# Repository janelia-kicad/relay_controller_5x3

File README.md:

# relay_controller_5x3

Authors:

    Peter Polidoro <polidorop@janelia.hhmi.org>

License:

    BSD

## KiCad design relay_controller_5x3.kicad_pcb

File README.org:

#+TITLE: relay_controller_5x3
#+AUTHOR: Peter Polidoro
#+EMAIL: peter@polidoro.io

* Repository Information
  - Author :: Peter Polidoro
  - License :: Open-Source Hardware

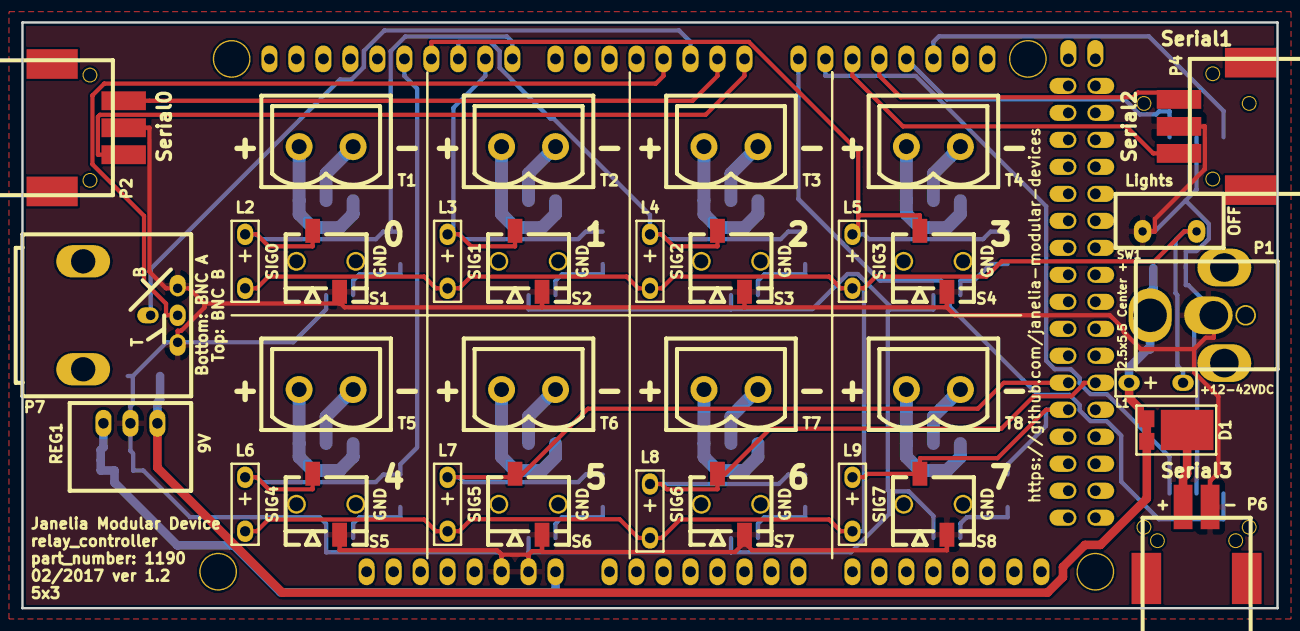
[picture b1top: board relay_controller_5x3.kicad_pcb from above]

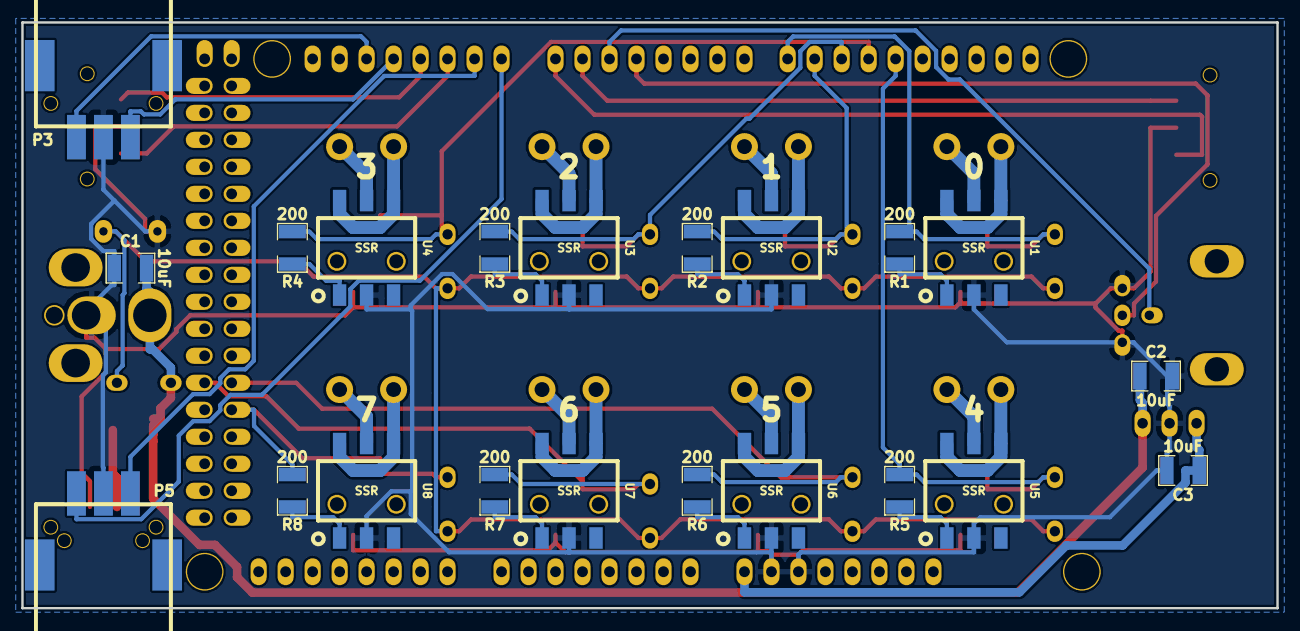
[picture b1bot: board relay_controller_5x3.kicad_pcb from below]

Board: 2 copper layers, 118.1 x 55.1 mm, 55 parts (21 on the bottom side), 47 nets.

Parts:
ARDUINO1: ARDUINO_MEGA; ARDUINO_MEGA_SHIELD
C1, C2, C3: 10uF; SM1210
D1: diode_schottky_45V_10A; CFP15
L1: LED_24V; LED_555-3XXX
L2, L3, L4, L5, L6, L7, L8, L9: LED_5V_GRN; LED_555-3XXX
P1: PWR_JACK_2.5x5.5; DCJACK_2PIN_HIGHCURRENT
P2, P3, P4, P5: HEADER_01X03_SMD_RA; Header_3_Pin_SMD_RA
P6: HEADER_01X02_SMD_RA; Header_2_Pin_SMD_RA
P7: BNC_DOUBLE_RA; BNC_DOUBLE
R1, R2, R3, R4, R5, R6, R7, R8: 200; SM1210
REG1: CONV_DC_DC_9V_1A; DC_DC_CONV_R78C
S1, S2, S3, S4, S5, S6, S7, S8: HEADER_01X02_SMD_SHR; Header_2_Pin_SMD_SHR
SW1: SPST_SLIDE_AS
T1, T2, T3, T4, T5, T6, T7, T8: TERM_BLK_HDR_2POS_VERT_0.2IN
U1, U2, U3, U4, U5, U6, U7, U8: SSR; 6-SMD-GW-0.3IN

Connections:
/BNC_A: ARDUINO1.2, P7.1
/BNC_B: ARDUINO1.3, P7.3
/LED_GND: L1.2, L2.2, L3.2, L4.2, L5.2, L6.2, L7.2, L8.2, L9.2, SW1.3
/OUT_0+: T1.1, U1.4, U1.6
/OUT_0-: T1.2, U1.5
/OUT_1+: T2.1, U2.4, U2.6
/OUT_1-: T2.2, U2.5
/OUT_2+: T3.1, U3.4, U3.6
/OUT_2-: T3.2, U3.5
/OUT_3+: T4.1, U4.4, U4.6
/OUT_3-: T4.2, U4.5
/OUT_4+: T5.1, U5.4, U5.6
/OUT_4-: T5.2, U5.5
/OUT_5+: T6.1, U6.4, U6.6
/OUT_5-: T6.2, U6.5
/OUT_6+: T7.1, U7.4, U7.6
/OUT_6-: T7.2, U7.5
/OUT_7+: T8.1, U8.4, U8.6
/OUT_7-: T8.2, U8.5
/RX0: ARDUINO1.0, P2.1
/RX1: ARDUINO1.19, P3.1
/RX2: ARDUINO1.17, P4.1
/RX3: ARDUINO1.15, P5.1
/SIGNAL_0: ARDUINO1.8, L2.1, R1.2, S1.1
/SIGNAL_1: ARDUINO1.9, L3.1, R2.2, S2.1
/SIGNAL_2: ARDUINO1.10, L4.1, R3.2, S3.1
/SIGNAL_3: ARDUINO1.11, L5.1, R4.2, S4.1
/SIGNAL_4: ARDUINO1.12, L6.1, R5.2, S5.1
/SIGNAL_5: ARDUINO1.44, L7.1, R6.2, S6.1
/SIGNAL_6: ARDUINO1.45, L8.1, R7.2, S7.1
/SIGNAL_7: ARDUINO1.46, L9.1, R8.2, S8.1
/TX0: ARDUINO1.1, P2.3
/TX1: ARDUINO1.18, P3.3
/TX2: ARDUINO1.16, P4.3
/TX3: ARDUINO1.14, P5.3
/V_IN: ARDUINO1.V_IN, C3.1, REG1.3
GND: ARDUINO1.GND1, ARDUINO1.GND2, C1.2, C2.2, C3.2, P1.2, P2.2, P3.2, P4.2, P5.2, P6.1, P7.2, P7.4, REG1.2, S1.2, S2.2, S3.2, S4.2, S5.2, S6.2, S7.2, S8.2, SW1.1, U1.2, U2.2, U3.2, U4.2, U5.2, U6.2, U7.2, U8.2
unnamed: R1.1, U1.1
unnamed: R2.1, U2.1
unnamed: R3.1, U3.1
unnamed: R4.1, U4.1
unnamed: R5.1, U5.1
unnamed: R6.1, U6.1
unnamed: R7.1, U7.1
unnamed: R8.1, U8.1
VAA: C1.1, C2.1, D1.2, L1.1, P1.1, REG1.1
VCC: D1.1, P6.2

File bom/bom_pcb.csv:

Item,Reference(s),Value,Quantity,Description,PartNumber,Vendor
1,ARDUINO1,ARDUINO_MEGA,1,BOARD MCU MEGA2560,1050-1018-ND,digikey
2,C1 C2 C3,10uF,3,CAP CER 10UF 50V 10% X7S 1210,445-4536-1-ND,digikey
3,D1,diode_schottky_45V_10A,1,DIODE SCHOTTKY 45V 10A CFP15,568-11697-1-ND,digikey
4,L1,LED_24V,1,LED 2MM 24V VERTICAL RED PC MNT,350-1723-ND,digikey
5,L2 L3 L4 L5 L6 L7 L8 L9,LED_5V_GRN,8,LED 2MM 5V VERTICAL GREEN PC MNT,350-1726-ND,digikey
6,P1,PWR_JACK_2.5x5.5,1,CONN PWR JACK DC 2.5X5.5 8A T/H,CP-063BH-ND,digikey
7,P2 P3 P4 P5,HEADER_01X03_SMD_RA,4,CONN HEADER 3POS R/A SMD GOLD,A100890CT-ND,digikey
8,P6,HEADER_01X02_SMD_RA,1,CONN HEADER 2POS R/A SMD GOLD,A100903CT-ND,digikey
9,P7,BNC_DOUBLE_RA,1,CONN BNC JACK R/A 75 OHM PCB,ACX1655-ND,digikey
10,R1 R2 R3 R4 R5 R6 R7 R8,200,8,200 Ohm 1% 0.5W 1210,P200AACT-ND,digikey
11,REG1,CONV_DC_DC_9V_1A,1,CONV DC/DC 1A 9V OUT SIP VERT,945-1396-5-ND,digikey
12,S1 S2 S3 S4 S5 S6 S7 S8,HEADER_01X02_SMD_SHR,8,CONN HEADER 2POS IDC SMD 30GOLD,A121539CT-ND,digikey
13,SW1,SPST_SLIDE_AS,1,SWITCH SLIDE SPST 0.4VA 28V,360-2610-ND,digikey
14,T1 T2 T3 T4 T5 T6 T7 T8,TERM_BLK_HDR_2POS_VERT_0.2IN,8,TERM BLOCK HDR 2POS VERT 5.08MM,277-1150-ND,digikey
15,U1 U2 U3 U4 U5 U6 U7 U8,SSR_DC_6PIN_2.5A,8,RELAY SSR SPST SGL 2.5A 6SMD GW,255-3375-1-ND,digikey

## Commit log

2017-01-04 Initial commit.
2017-01-04 Modified paths.
2017-01-04 Remove local paths.
2017-01-13 Progress towards v1.2.
2017-01-17 Added signal outputs.
2017-01-18 Added Header_2_Pin_SMD_SHR.
2017-01-18 Changed to shrouded headers.
2017-02-01 Updated relays and resistors.
2017-02-01 Progress towards next version.
2017-02-02 Finished v1.2.
2017-03-24 Updated documentation.
2017-06-15 Removed .cmp file.
2017-09-22 Removed extra libraries.
2018-01-08 Updated to v4.
2018-01-08 Added v4 files.
2018-01-08 Updated gitignore.
2018-03-09 Update license from software to hardware.
2018-04-12 README.md -> README.org.
2018-04-19 Added .DS_Store to .gitignore.
2018-05-16 Added generate_kicad_documentation submodule.
2018-05-17 Updated submodules.
2018-08-12 Removed v4 files.
2018-08-24 Removed F.SilkS from pads.
2018-08-27 Removed *.SilkS from pads.
2021-09-16 Update email address
2021-09-21 Remove ignored files
2022-02-22 Add guix files
2022-02-23 Add guix documentation
